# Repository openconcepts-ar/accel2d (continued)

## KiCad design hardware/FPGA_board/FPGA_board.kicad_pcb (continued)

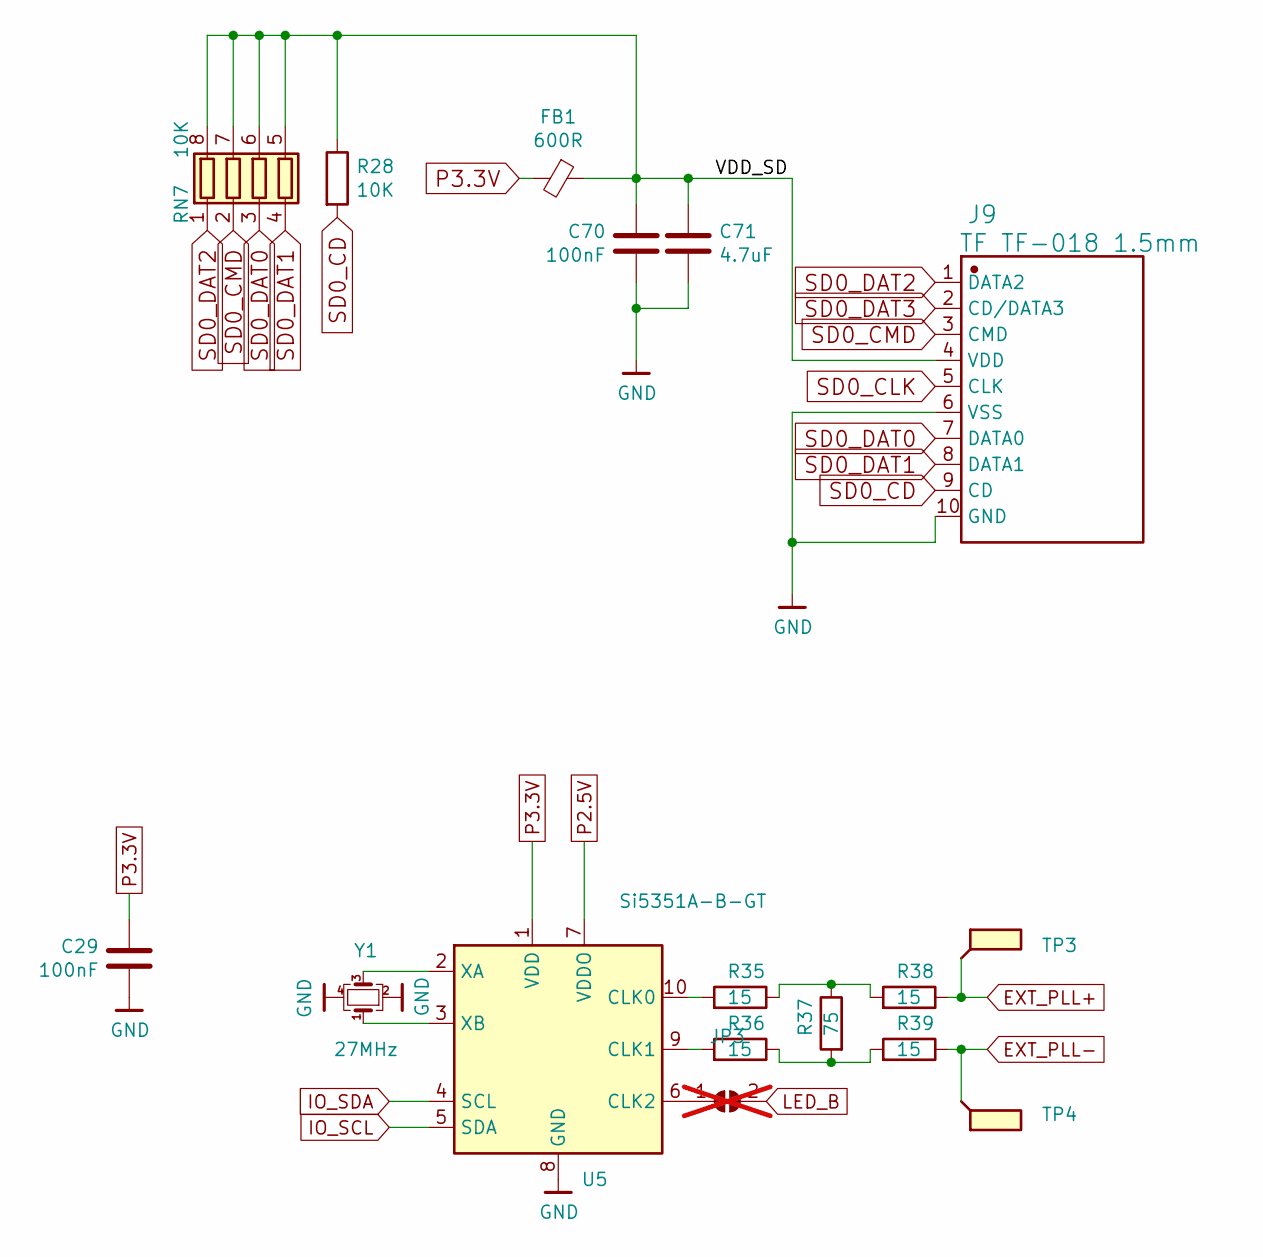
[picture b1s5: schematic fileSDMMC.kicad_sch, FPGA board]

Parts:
C29, C70: 100nF; C_0201_0603Metric; MPN CL03A104KQ3NNNC
C71: 4.7uF; C_0603_1608Metric; MPN CL10A475KP8NNNC
FB1: 600R; L_0402_1005Metric; MPN BLM15AG601SN1D
J9: TF TF-018 1.5mm; TF-SMD_TF-018; MPN TF-018
JP3: SolderJumper_2_Open; SolderJumper-2_P1.3mm_Open_RoundedPad1.0x1.5mm; not fitted
R28: 10K; R_0201_0603Metric
R35, R36, R38, R39: 15; R_0201_0603Metric; MPN RC0201FR-074K7L
R37: 75; R_0201_0603Metric; MPN RC0201FR-074K7L
RN7: 10K; R_Array_Convex_4x0402; MPN 4D02WGJ0103TCE
TP3, TP4: SMD_TP; TestPoint_Pad_D1.0mm
U5: Si5351A-B-GT; MSOP-10_3x3mm_P0.5mm; MPN SI5351A-B-GTR
Y1: 27MHz; Crystal_SMD_2016-4Pin_2.0x1.6mm; MPN XL7EL89COI-111YLC-27M; LCSC Part Number C18214311

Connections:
/sheetSDMMC/VDD_SD: C70.2, C71.1, FB1.1, J9.4 (VDD), R28.1, RN7.5 (R4.2), RN7.6 (R3.2), RN7.7 (R2.2), RN7.8 (R1.2)
EXT_PLL+: R38.1, TP3.1; also elsewhere on the board
EXT_PLL-: R39.1, TP4.1; also elsewhere on the board
GND: C29.1, C70.1, C71.2, J9.6 (VSS), J9.10 (GND), U5.8 (GND), Y1.2, Y1.4; also elsewhere on the board
IO_SCL: U5.5 (SDA); also elsewhere on the board
IO_SDA: U5.4 (SCL); also elsewhere on the board
unnamed: R35.1, R37.1, R38.2
unnamed: R36.1, R37.2, R39.2
unnamed: R35.2, U5.10 (CLK0)
unnamed: R36.2, U5.9 (CLK1)
unnamed: JP3.1 (A), U5.6 (CLK2)
unnamed: U5.2 (XA), Y1.3
unnamed: U5.3 (XB), Y1.1
P2.5V: U5.7 (VDDO); also elsewhere on the board
P3.3V: C29.2, FB1.2, U5.1 (VDD); also elsewhere on the board
SD0_CD: J9.9 (CD), R28.2; also elsewhere on the board
SD0_CLK: J9.5 (CLK); also elsewhere on the board
SD0_CMD: J9.3 (CMD), RN7.2 (R2.1); also elsewhere on the board
SD0_DAT0: J9.7 (DATA0), RN7.3 (R3.1); also elsewhere on the board
SD0_DAT1: J9.8 (DATA1), RN7.4 (R4.1); also elsewhere on the board
SD0_DAT2: J9.1 (DATA2), RN7.1 (R1.1); also elsewhere on the board
SD0_DAT3: J9.2 (CD/DATA3); also elsewhere on the board

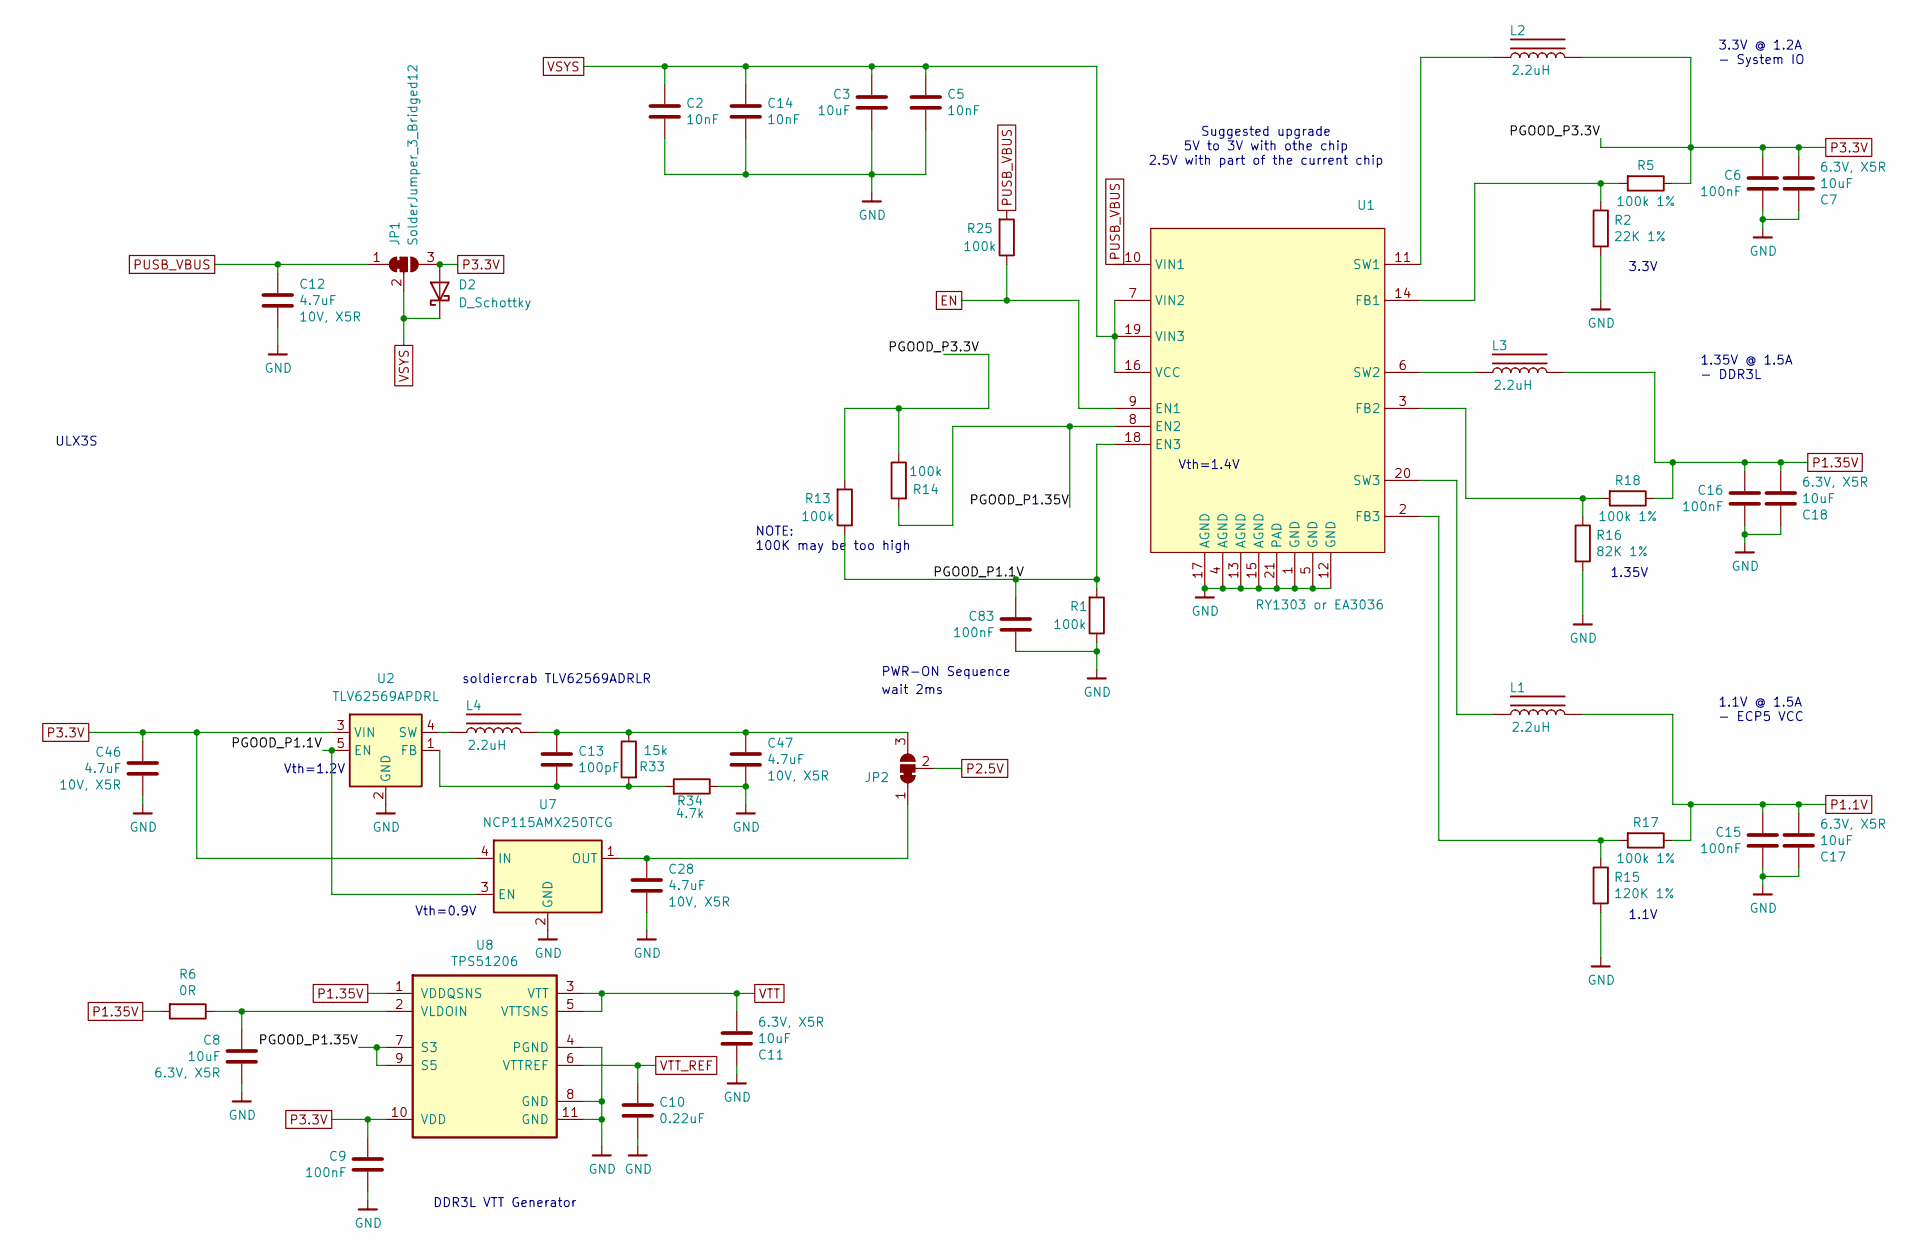
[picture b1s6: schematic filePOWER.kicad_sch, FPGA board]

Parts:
C2, C5, C14: 10nF; C_0201_0603Metric; MPN GRM033R61C103KA12D
C3: 10uF; C_0603_1608Metric; MPN LMK107BBJ106MALT
C6, C9, C15, C16, C83: 100nF; C_0201_0603Metric; MPN CL03A104KQ3NNNC
C7, C8, C11, C17, C18: 10uF; C_0402_1005Metric; MPN GRM155R60J106ME44D
C10: 0.22uF; C_0201_0603Metric; MPN CL03A224MQ3NNNC
C12, C28, C46, C47: 4.7uF; C_0402_1005Metric; MPN GRM155R61A475MEAAD
C13: 100pF; C_0201_0603Metric; MPN GRM033R61C103KA12D
D2: D_Schottky; U-DFN1608-2_L1.6-W0.8-RD; MPN PMEG4020EPK,315
JP1, JP2: SolderJumper_3_Bridged12; SolderJumper-3_P1.3mm_Bridged12_RoundedPad1.0x1.5mm
L1, L2, L3, L4: 2.2uH; Murata_DFE201612P-2R2M=P2; LCSC Part Number C79317
R1, R13, R14, R25: 100k; R_0201_0603Metric; MPN RC0201FR-07100KL
R2: 22K 1%; R_0402_1005Metric
R5, R17, R18: 100k 1%; R_0201_0603Metric; MPN RC0201FR-07100KL
R6: 0R; R_0402_1005Metric; MPN RC0402FR-070RL
R15: 120K 1%; R_0402_1005Metric
R16: 82K 1%; R_0402_1005Metric
R33: 15k; R_0201_0603Metric; MPN RC0201FR-07100KL
R34: 4.7k; R_0201_0603Metric; MPN RC0201FR-07100KL
U1: RY1303 or EA3036; QFN-20-1EP_3x3mm_P0.4mm_EP1.65x1.65mm; MPN EA3036CQBR
U2: TLV62569APDRL; SOT-563; MPN TLV62569APDRLR
U7: NCP115AMX250TCG; OnSemi_XDFN4-1EP_1.0x1.0mm_EP0.52x0.52mm; MPN NCP115AMX250TCG
U8: TPS51206; WSON-10-1EP_2x2mm_P0.4mm; MPN TPS51206DSQR

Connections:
/sheetPower/PGOOD_P1.1V: C83.2, R1.2, R13.1, U1.18 (EN3), U2.5 (EN), U7.3 (EN)
/sheetPower/PGOOD_P1.35V: R14.2, U1.8 (EN2), U8.7 (S3), U8.9 (S5)
EN: R25.1, U1.9 (EN1)
GND: C2.1, C3.1, C5.1, C6.1, C7.2, C8.1, C9.1, C10.1, C11.2, C12.2, C14.1, C15.1, C16.1, C17.2, C18.2, C28.2, C46.2, C47.2, C83.1, R1.1, R2.2, R15.2, R16.2, R34.1, U1.1 (GND), U1.4 (AGND), U1.5 (GND), U1.12 (GND), U1.13 (AGND), U1.15 (AGND), U1.17 (AGND), U1.21 (PAD), U2.2 (GND), U7.2 (GND), U7.5 (GND), U8.4 (PGND), U8.8 (GND), U8.11 (GND); also elsewhere on the board
unnamed: C28.1, JP2.1 (A), U7.1 (OUT)
unnamed: C13.2, C47.1, JP2.3 (B), L4.1, R33.1
unnamed: R2.1, R5.2, U1.14 (FB1)
unnamed: R16.1, R18.2, U1.3 (FB2)
unnamed: R15.1, R17.2, U1.2 (FB3)
unnamed: L2.2, U1.11 (SW1)
unnamed: L3.2, U1.6 (SW2)
unnamed: L1.2, U1.20 (SW3)
unnamed: C13.1, R33.2, R34.2, U2.1 (FB)
unnamed: L4.2, U2.4 (SW)
unnamed: C8.2, R6.1, U8.2 (VLDOIN)
P1.1V: C15.2, C17.1, L1.1, R17.1; also elsewhere on the board
P1.35V: C16.2, C18.1, L3.1, R6.2, R18.1, U8.1 (VDDQSNS); also elsewhere on the board
P2.5V: JP2.2 (C); also elsewhere on the board
P3.3V: C6.2, C7.1, C9.2, C46.1, D2.2 (A), JP1.3 (B), L2.1, R5.1, R13.2, R14.1, U2.3 (VIN), U7.4 (IN), U8.10 (VDD); also elsewhere on the board
PUSB_VBUS: C12.1, JP1.1 (A), R25.2, U1.10 (VIN1); also elsewhere on the board
VSYS: C2.2, C3.2, C5.2, C14.2, D2.1 (K), JP1.2 (C), U1.7 (VIN2), U1.16 (VCC), U1.19 (VIN3)
VTT: C11.1, U8.3 (VTT), U8.5 (VTTSNS); also elsewhere on the board
VTT_REF: C10.2, U8.6 (VTTREF); also elsewhere on the board

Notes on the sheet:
1.1V @ 1.5A - ECP5 VCC
PWR-ON Sequence
Vth=0.9V
NOTE: 100K may be too high
1.35V @ 1.5A - DDR3L
soldiercrab TLV62569ADRLR
DDR3L VTT Generator
Suggested upgrade 5V to 3V with othe chip 2.5V with part of the current chip
1.1V
3.3V @ 1.2A - System IO
3.3V
wait 2ms
Vth=1.4V
ULX3S
1.35V
Vth=1.2V

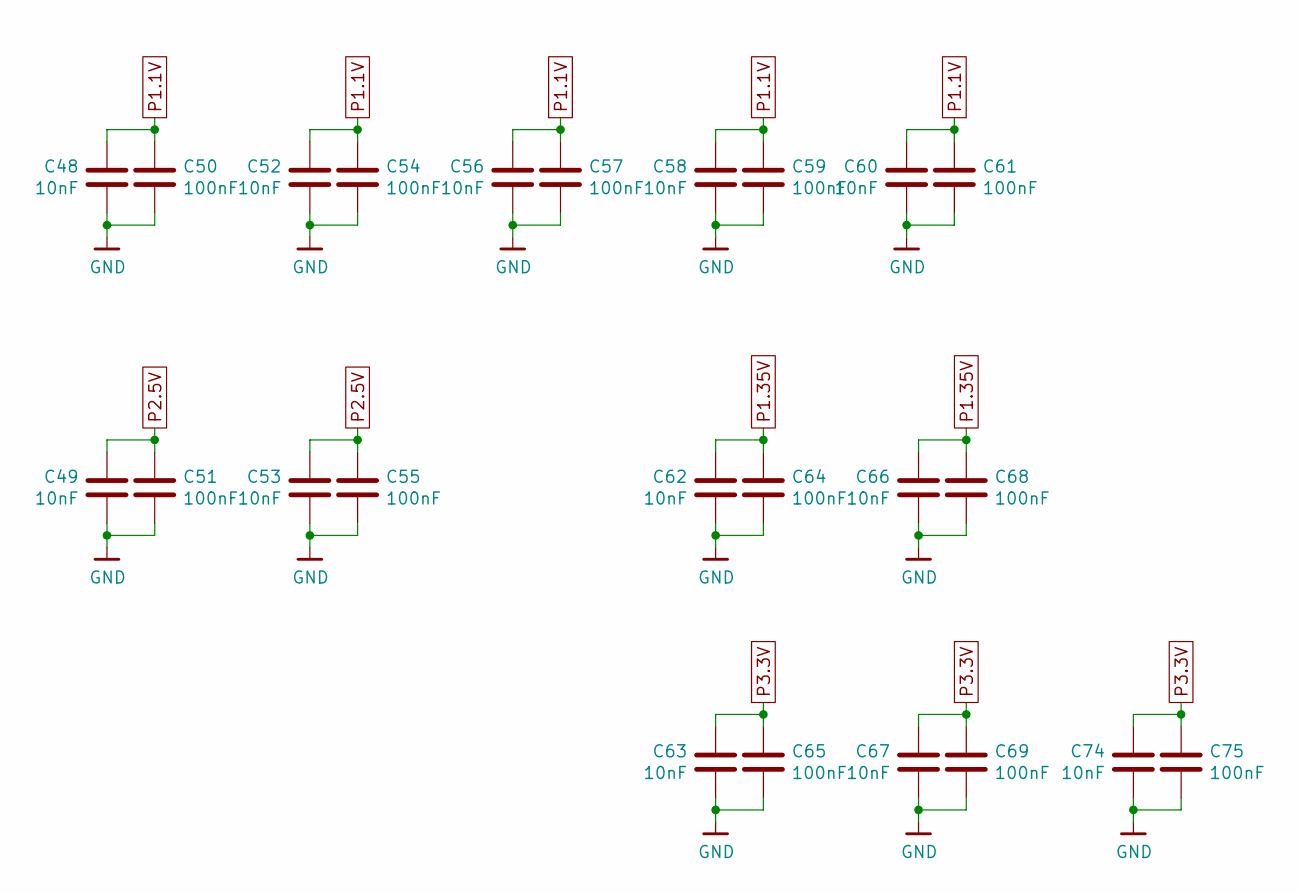
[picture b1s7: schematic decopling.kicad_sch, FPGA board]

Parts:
C48, C49, C52, C53, C56, C58, C60, C62, C63, C66, C67, C74: 10nF; C_0201_0603Metric; MPN GRM033R61C103KA12D
C50, C51, C54, C55, C57, C59, C61, C64, C65, C68, C69, C75: 100nF; C_0201_0603Metric; MPN CL03A104KQ3NNNC

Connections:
GND: C48.2, C49.2, C50.2, C51.2, C52.2, C53.2, C54.2, C55.2, C56.2, C57.2, C58.2, C59.2, C60.2, C61.2, C62.2, C63.2, C64.2, C65.2, C66.2, C67.2, C68.2, C69.2, C74.2, C75.2; also elsewhere on the board
P1.1V: C48.1, C50.1, C52.1, C54.1, C56.1, C57.1, C58.1, C59.1, C60.1, C61.1; also elsewhere on the board
P1.35V: C62.1, C64.1, C66.1, C68.1; also elsewhere on the board
P2.5V: C49.1, C51.1, C53.1, C55.1; also elsewhere on the board
P3.3V: C63.1, C65.1, C67.1, C69.1, C74.1, C75.1; also elsewhere on the board

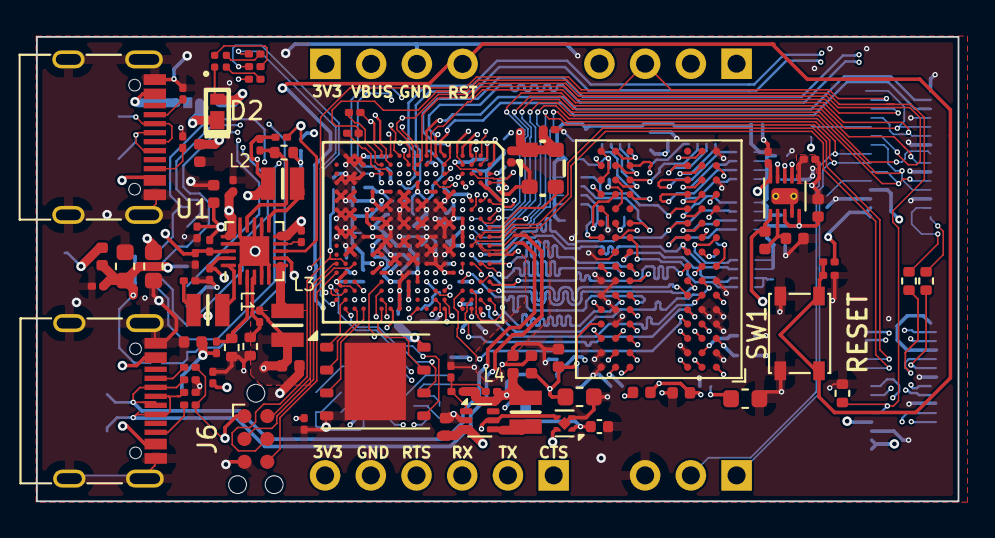
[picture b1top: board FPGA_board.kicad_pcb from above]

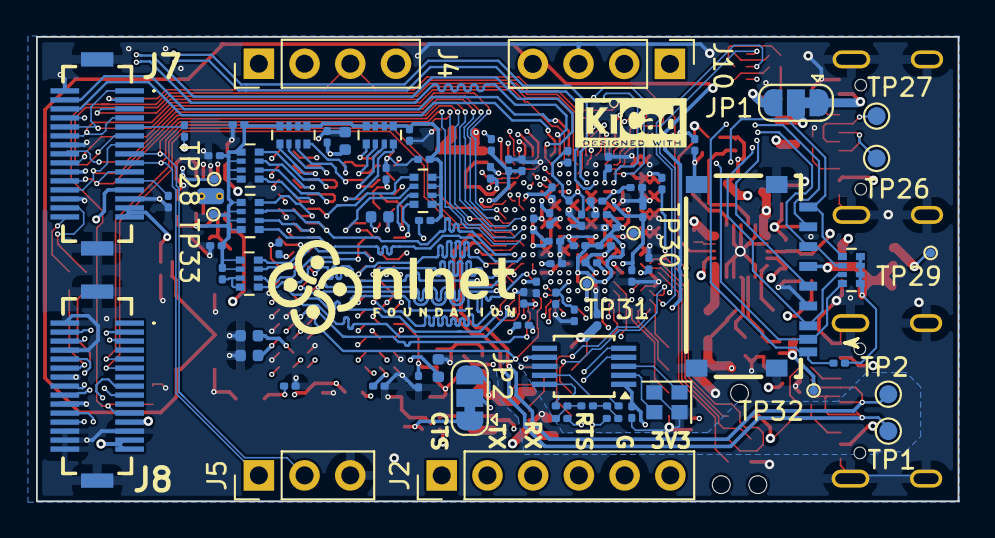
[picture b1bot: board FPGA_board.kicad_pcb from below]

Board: 6 copper layers, 51.2 x 25.8 mm, 163 parts (86 on the bottom side), 154 nets.

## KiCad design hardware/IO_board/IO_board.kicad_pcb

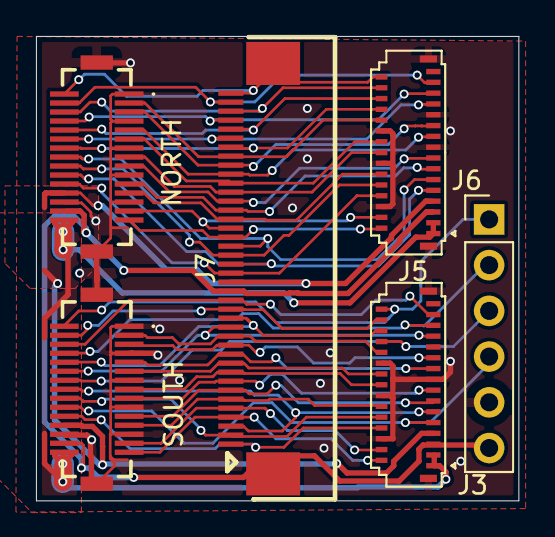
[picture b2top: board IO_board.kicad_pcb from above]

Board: 2 copper layers, 26.8 x 25.8 mm, 6 parts (0 on the bottom side), 46 nets.

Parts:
J1, J4: DF12NB(3.0)-30DS-0.5V(51); DF12NB3030DP05V51
J3, J5: Conn_01x31; Hirose_FH26-31S-0.3SHW_2Rows-31Pins-1MP_P0.60mm_Horizontal
J6: Conn_01x06; PinHeader_1x06_P2.54mm_Vertical
J7: Combined I/O; FPC-SMD_40P-P0.50_L4.4-W25.6

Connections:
/3V3: J1.30 (29), J3.1, J3.3, J4.30 (29), J5.1, J5.3
/5V0: J1.24 (23), J3.7, J4.24 (23), J5.7, J7.19
/B0: J1.8 (7), J5.27, J7.37
/B1: J1.2 (1), J5.30, J7.40
/B6: J1.27 (28), J5.4, J7.25
/B7: J1.29 (30), J5.2, J7.24
/BL_EN: J3.26, J4.10 (9), J7.15
/BL_PWM: J3.25, J4.12 (11), J7.14
/CK+: J3.22, J4.3 (4), J7.13
/CK-: J3.21, J4.5 (6), J7.12
/DE: J1.6 (5), J5.28, J7.38
/G0: J1.20 (19), J5.9, J7.21
/G1: J1.14 (13), J5.24, J7.34
/G4: J3.29, J4.6 (5), J7.17
/G5: J3.28, J4.4 (3), J7.16
/HPD2: J3.8, J4.22 (21), J7.1
/HPD/ID: J1.22 (21), J5.8, J7.20
/HSYNC: J1.10 (9), J5.26, J7.36
/LVDS_E0+: J3.13, J4.21 (22), J7.7
/LVDS_E0-: J3.12, J4.23 (24), J7.6
/LVDS_E1+: J3.16, J4.15 (16), J7.9
/LVDS_E1-: J3.15, J4.17 (18), J7.8
/LVDS_E2+: J3.19, J4.9 (10), J7.11
/LVDS_E2-: J3.18, J4.11 (12), J7.10
/LVDS_O0+: J1.21 (22), J5.13, J7.27
/LVDS_O0-: J1.23 (24), J5.12, J7.26
/LVDS_O1+: J1.15 (16), J5.16, J7.29
/LVDS_O1-: J1.17 (18), J5.15, J7.28
/LVDS_O2+: J1.9 (10), J5.19, J7.31
/LVDS_O2-: J1.11 (12), J5.18, J7.30
/LVDS_OC+: J1.3 (4), J5.22, J7.33
/LVDS_OC-: J1.5 (6), J5.21, J7.32
/PCLK: J1.4 (3), J5.29, J7.39
/R0: J3.4, J4.27 (28), J7.5
/R1: J3.2, J4.29 (30), J7.4
/SCL: J1.18 (17), J5.10, J7.22
/SCL2: J3.10, J4.18 (17), J7.2
/SDA: J1.16 (15), J5.11, J7.23
/SDA2: J3.11, J4.16 (15), J7.3
/TP_X1: J3.9, J4.20 (19), J6.4
/TP_X2: J3.24, J4.14 (13), J6.3
/TP_Y1: J3.30, J4.2 (1), J6.1
/TP_Y2: J3.27, J4.8 (7), J6.2
/VIO: J1.28 (27), J3.5, J4.28 (27), J5.5, J6.6, J7.18
/VSYNC: J1.12 (11), J5.25, J7.35
GND: J1.1 (2), J1.7 (8), J1.13 (14), J1.19 (20), J1.25 (26), J1.26 (25), J1.MP1, J1.MP2, J3.6, J3.14, J3.17, J3.20, J3.23, J3.MP (MountPin), J4.1 (2), J4.7 (8), J4.13 (14), J4.19 (20), J4.25 (26), J4.26 (25), J4.MP1, J4.MP2, J5.6, J5.14, J5.17, J5.20, J5.23, J5.MP (MountPin), J6.5

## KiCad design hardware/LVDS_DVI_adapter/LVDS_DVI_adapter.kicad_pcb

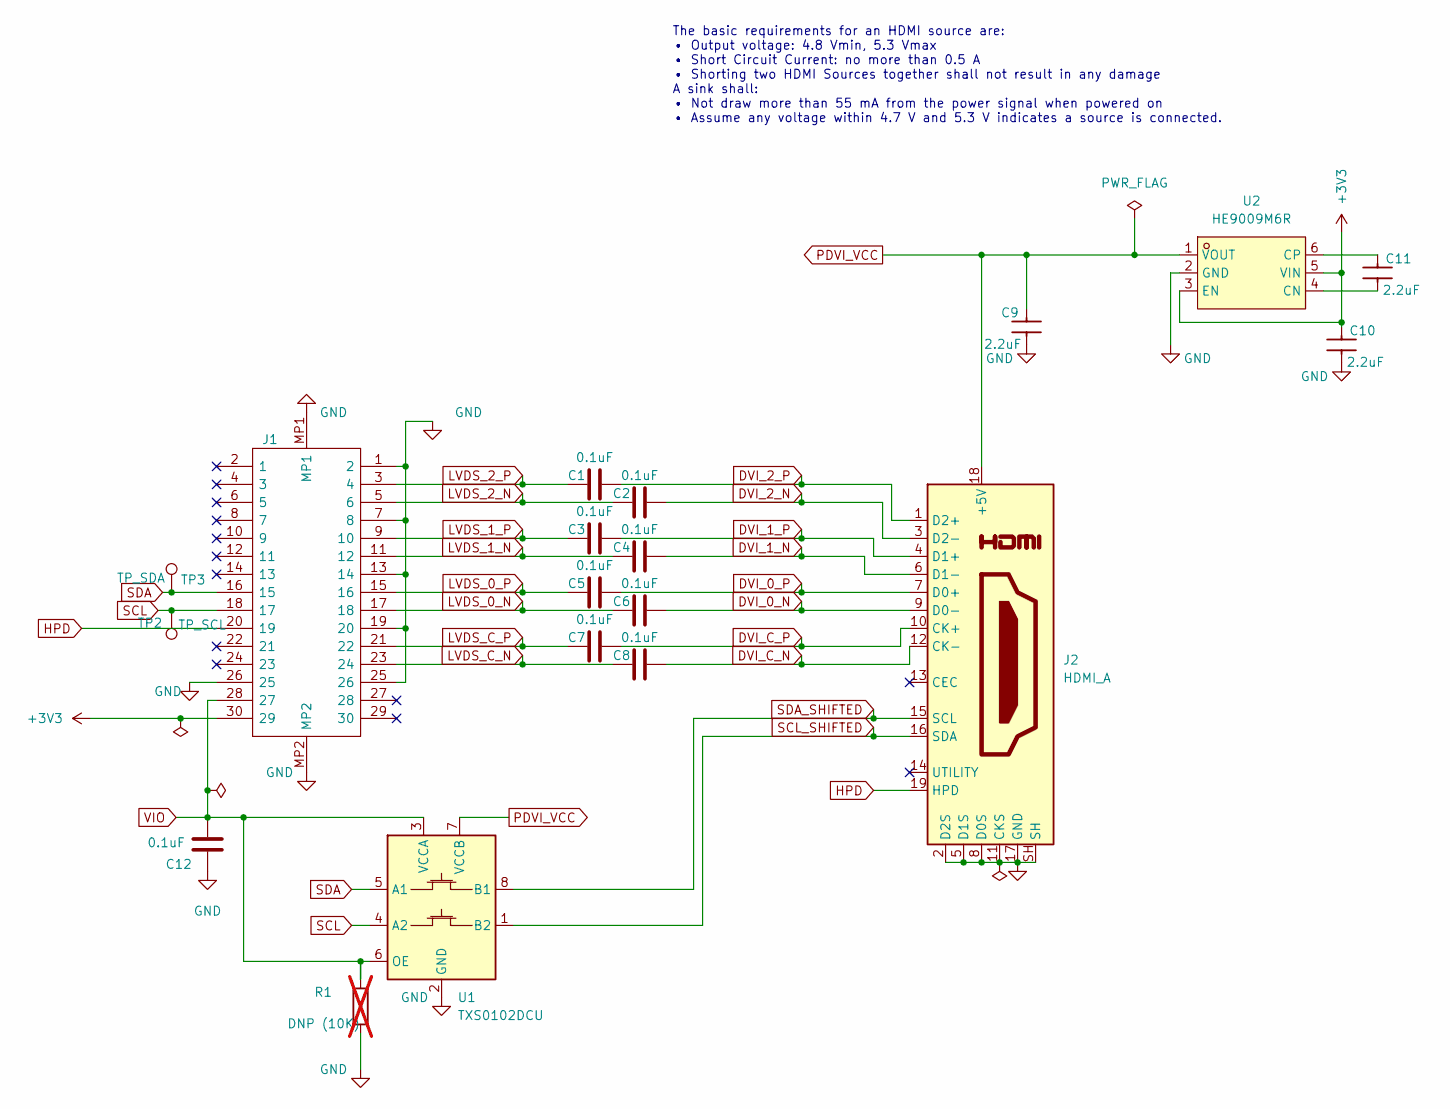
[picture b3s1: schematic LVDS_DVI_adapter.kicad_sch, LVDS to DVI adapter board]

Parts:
C1, C2, C3, C4, C5, C6, C8, C12: 0.1uF; C_0402_1005Metric; LCSC Part number C60474
C7: 0.1uF; C_0402_1005Metric; LCSC Part Number C60474
C9, C10, C11: 2.2uF; C_0402_1005Metric; LCSC Part Number C170151
J1: DF12NB(3.0)-30DS-0.5V(51); DF12NB3030DP05V51; Manufacturer_Part_Number DF12NB(3.0)-30DP-0.5V(51); LCSC Part Number C2904115
J2: HDMI_A; HDMI_A_Amphenol_10029449-x01xLF_Horizontal; LCSC Part number C427307
R1: DNP (10K); R_0402_1005Metric; LCSC Part Number C25531; not fitted
TP2: TP_SCL; TestPoint_THTPad_1.0x1.0mm_Drill0.5mm
TP3: TP_SDA; TestPoint_THTPad_1.0x1.0mm_Drill0.5mm
U1: TXS0102DCU; VSSOP-8_2.3x2mm_P0.5mm; LCSC Part Number C53434
U2: HE9009M6R; SOT-23-6; MPN HE9009M6R

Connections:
+3V3: C10.1, J1.30 (29), U2.3 (EN), U2.5 (VIN)
DVI_0_N: C6.2, J2.9 (D0-)
DVI_0_P: C5.2, J2.7 (D0+)
DVI_1_N: C4.2, J2.6 (D1-)
DVI_1_P: C3.2, J2.4 (D1+)
DVI_2_N: C2.2, J2.3 (D2-)
DVI_2_P: C1.2, J2.1 (D2+)
DVI_C_N: C8.2, J2.12 (CK-)
DVI_C_P: C7.2, J2.10 (CK+)
GND: C9.2, C10.2, C12.1, J1.1 (2), J1.7 (8), J1.13 (14), J1.19 (20), J1.25 (26), J1.26 (25), J1.MP1, J1.MP2, J2.2 (D2S), J2.5 (D1S), J2.8 (D0S), J2.11 (CKS), J2.17 (GND), J2.SH, R1.2, U1.2 (GND), U2.2 (GND)
HPD: J1.20 (19), J2.19 (HPD)
LVDS_0_N: C6.1, J1.17 (18)
LVDS_0_P: C5.1, J1.15 (16)
LVDS_1_N: C4.1, J1.11 (12)
LVDS_1_P: C3.1, J1.9 (10)
LVDS_2_N: C2.1, J1.5 (6)
LVDS_2_P: C1.1, J1.3 (4)
LVDS_C_N: C8.1, J1.23 (24)
LVDS_C_P: C7.1, J1.21 (22)
unnamed: C11.2, U2.4 (CN)
unnamed: C11.1, U2.6 (CP)
PDVI_VCC: C9.1, J2.18 (+5V), U1.7 (VCCB), U2.1 (VOUT)
SCL: J1.18 (17), TP2.1, U1.4 (A2)
SCL_SHIFTED: J2.16 (SDA), U1.1 (B2)
SDA: J1.16 (15), TP3.1, U1.5 (A1)
SDA_SHIFTED: J2.15 (SCL), U1.8 (B1)
VIO: C12.2, J1.28 (27), R1.1, U1.3 (VCCA), U1.6 (OE)

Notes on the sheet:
The basic requirements for an HDMI source are: • Output voltage: 4.8 Vmin, 5.3 Vmax • Short Circuit Current: no more than 0.5 A • Shorting two HDMI Sources together shall not result in any damage A sink shall: • Not draw more than 55 mA from the power signal when powered on • Assume any voltage wit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

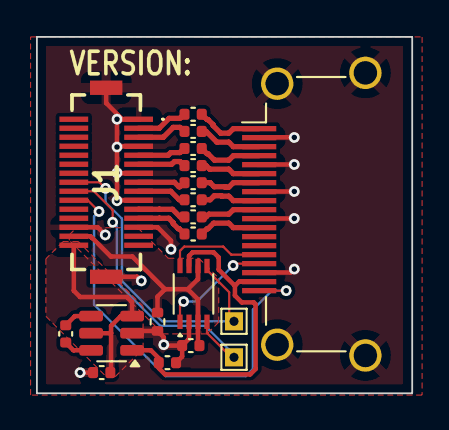
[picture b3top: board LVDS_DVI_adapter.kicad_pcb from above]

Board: 2 copper layers, 20.9 x 19.8 mm, 19 parts (0 on the bottom side), 27 nets.

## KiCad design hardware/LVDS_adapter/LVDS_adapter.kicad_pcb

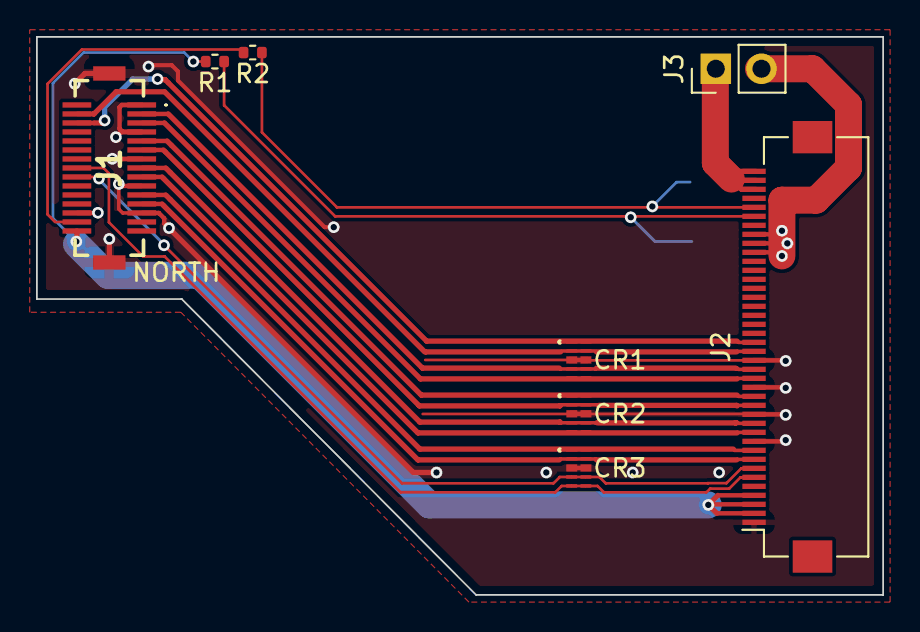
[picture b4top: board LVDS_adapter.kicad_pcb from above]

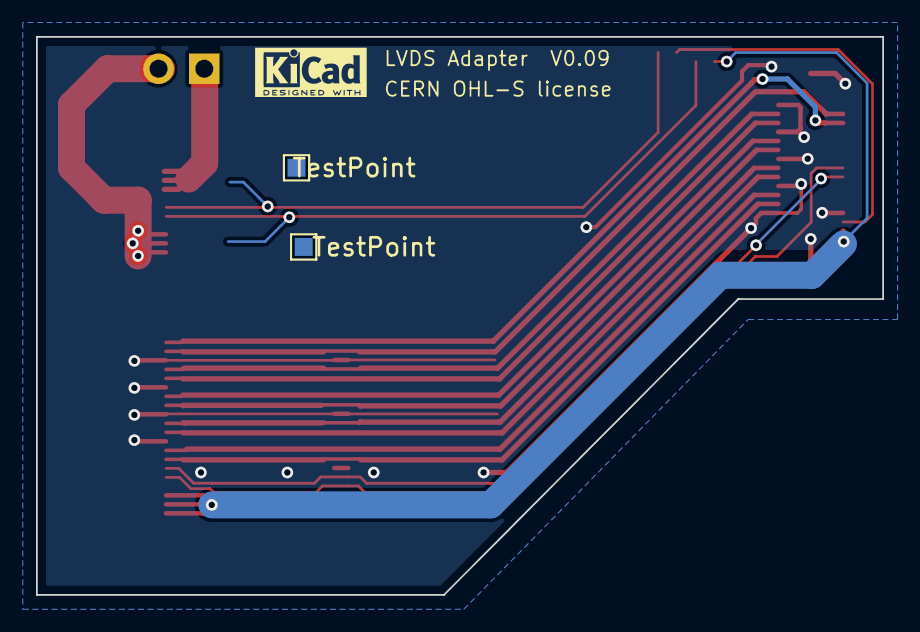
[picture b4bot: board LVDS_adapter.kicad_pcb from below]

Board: 2 copper layers, 47.0 x 31.0 mm, 10 parts (2 on the bottom side), 19 nets.

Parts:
CR1, CR2, CR3: ESD7004MUTAG; UDFN10_517BB_ONS-L
J1: DF12NB(3.0)-30DS-0.5V(51); DF12NB3030DP05V51
J2: LVDS; Hirose_FH12-40S-0.5SH_1x40-1MP_P0.50mm_Horizontal
J3: BAKLIGHT_POWER; PinHeader_1x02_P2.54mm_Vertical
R1, R2: 10K; R_0402_1005Metric
TP1, TP2: TestPoint; TestPoint_Pad_1.0x1.0mm

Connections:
GND: CR1.3, CR1.8, CR2.3, CR2.8, CR3.3, CR3.8, J1.1 (2), J1.7 (8), J1.13 (14), J1.19 (20), J1.25 (26), J1.26 (25), J1.MP1, J1.MP2, J2.1, J2.10, J2.13, J2.16, J2.19
LED_VCC: J2.38, J2.39, J2.40, J3.1
LVDS_O0_N: CR3.2, CR3.9, J1.23 (24), J2.8
LVDS_O0_P: CR3.1, CR3.10, J1.21 (22), J2.9
LVDS_O1_N: CR2.5, CR2.6, J1.17 (18), J2.11
LVDS_O1_P: CR2.4, CR2.7, J1.15 (16), J2.12
LVDS_O2_N: CR2.2, CR2.9, J1.11 (12), J2.14
LVDS_O2_P: CR2.1, CR2.10, J1.9 (10), J2.15
LVDS_O3_N: CR1.2, CR1.9, J1.4 (3), J2.20
LVDS_O3_P: CR1.1, CR1.10, J1.6 (5), J2.21
LVDS_OC_N: CR1.5, CR1.6, J1.5 (6), J2.17
LVDS_OC_P: CR1.4, CR1.7, J1.3 (4), J2.18
unnamed: J1.28 (27), R2.2
unnamed: J2.31, J2.32, J2.33, J3.2
unnamed: J2.35, R1.1, TP2.1
unnamed: J2.36, R2.1, TP1.1
SCL: CR3.4, CR3.7, J1.18 (17), J2.7
SDA: CR3.5, CR3.6, J1.16 (15), J2.6
VCC: J1.30 (29), J2.2, J2.3, J2.4, R1.2

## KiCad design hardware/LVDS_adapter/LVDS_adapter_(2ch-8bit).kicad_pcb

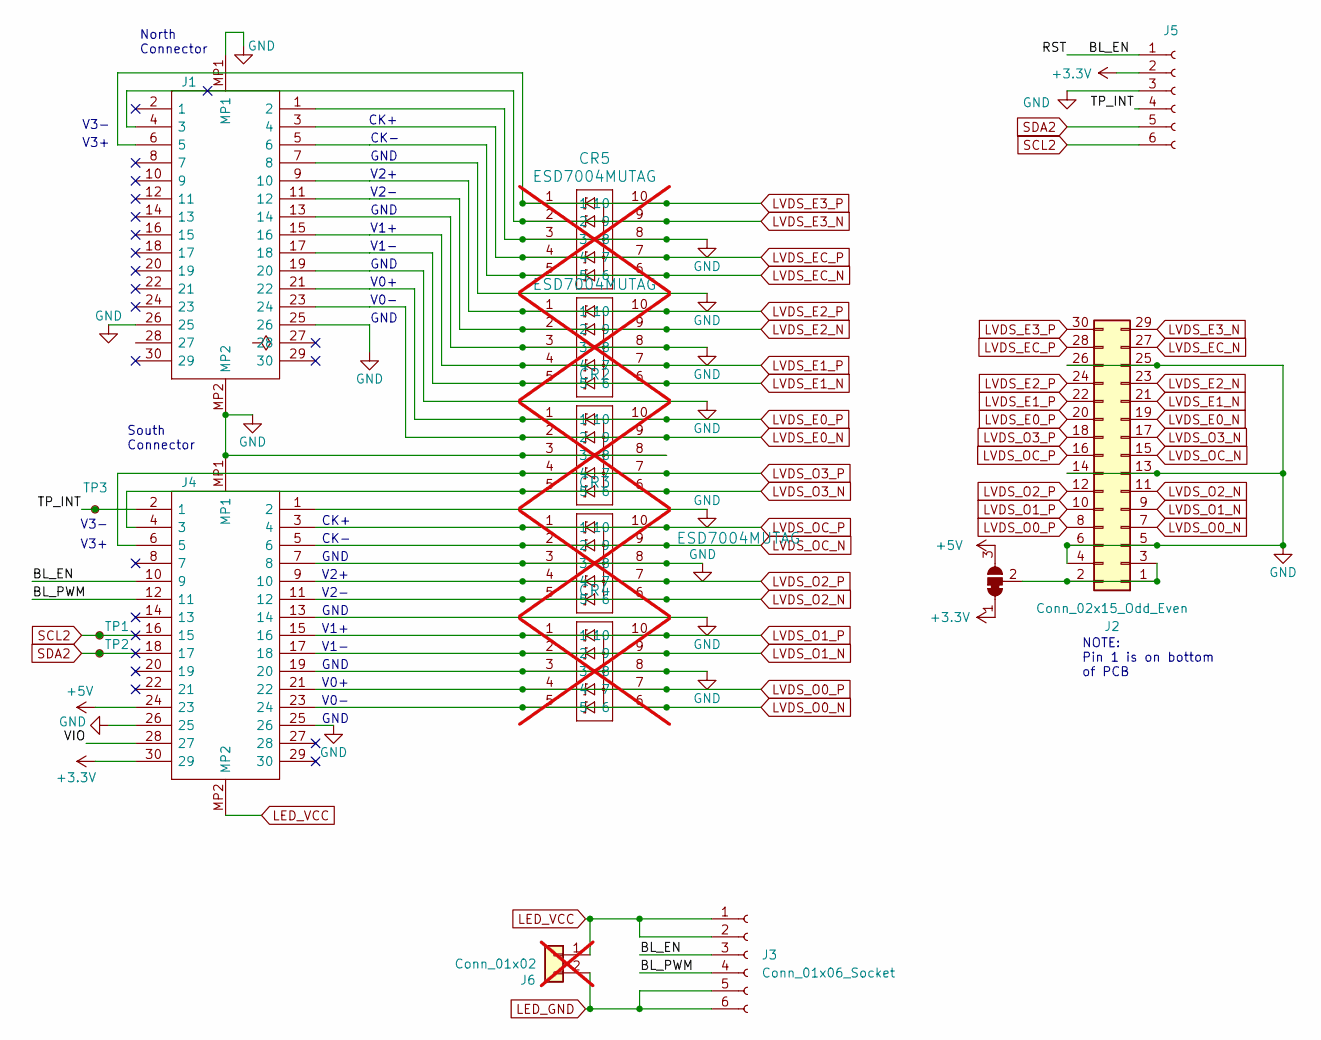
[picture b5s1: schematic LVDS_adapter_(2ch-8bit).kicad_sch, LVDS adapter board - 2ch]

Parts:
CR1, CR2, CR3, CR4, CR5: ESD7004MUTAG; Diodes_UDFN-10_1.0x2.5mm_P0.5mm; LCSC Part Number C2931115; not fitted
J1, J4: DF12NB(3.0)-30DS-0.5V(51); DF12NB3030DP05V51; Manufacturer_Part_Number DF12NB(3.0)-30DP-0.5V(51); LCSC Part Number C2904115
J2: Conn_02x15_Odd_Even; PinHeader_2x15_P2.00mm_Vertical
J3: Conn_01x06_Socket; JST_PH_S6B-PH-K_1x06_P2.00mm_Horizontal; MPN S6B-PH-K-S(LF)(SN)
J5: Conn_01x06_Socket; FPC-SMD_FH52K-6S-0.5SH; MPN FH52K-6S-0.5SH
J6: Conn_01x02; PinHeader_1x02_P2.54mm_Vertical; not fitted
JP1: SolderJumper_3_Bridged12; SolderJumper-3_P1.3mm_Bridged12_RoundedPad1.0x1.5mm
TP1, TP2, TP3: TestPoint_Small; TestPoint_Pad_D1.0mm

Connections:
+3.3V: J4.30 (29), J5.2, JP1.1 (A)
+5V: J4.24 (23), JP1.3 (B)
/BL_EN: J3.3, J4.10 (9), J5.1
/BL_PWM: J3.4, J4.12 (11)
/TP_INT: J4.2 (1), J5.4, TP3.1
/VIO: J4.28 (27)
GND: CR1.3, CR1.8, CR2.3, CR2.8, CR3.3, CR3.8, CR4.3, CR4.8, CR5.3, CR5.8, J1.1 (2), J1.7 (8), J1.13 (14), J1.19 (20), J1.25 (26), J1.26 (25), J1.MP1, J1.MP2, J2.4, J2.5, J2.6, J2.13, J2.14, J2.25, J2.26, J4.1 (2), J4.7 (8), J4.13 (14), J4.19 (20), J4.25 (26), J4.26 (25), J4.MP1, J5.3
LED_GND: J3.5, J3.6, J6.2
LED_VCC: J3.1, J3.2, J4.MP2, J6.1
LVDS_E0_N: CR2.2, CR2.9, J1.23 (24), J2.19
LVDS_E0_P: CR2.1, CR2.10, J1.21 (22), J2.20
LVDS_E1_N: CR1.5, CR1.6, J1.17 (18), J2.21
LVDS_E1_P: CR1.4, CR1.7, J1.15 (16), J2.22
LVDS_E2_N: CR1.2, CR1.9, J1.11 (12), J2.23
LVDS_E2_P: CR1.1, CR1.10, J1.9 (10), J2.24
LVDS_E3_N: CR5.2, CR5.9, J1.4 (3), J2.29
LVDS_E3_P: CR5.1, CR5.10, J1.6 (5), J2.30
LVDS_EC_N: CR5.5, CR5.6, J1.5 (6), J2.27
LVDS_EC_P: CR5.4, CR5.7, J1.3 (4), J2.28
LVDS_O0_N: CR4.5, CR4.6, J2.7, J4.23 (24)
LVDS_O0_P: CR4.4, CR4.7, J2.8, J4.21 (22)
LVDS_O1_N: CR4.2, CR4.9, J2.9, J4.17 (18)
LVDS_O1_P: CR4.1, CR4.10, J2.10, J4.15 (16)
LVDS_O2_N: CR3.5, CR3.6, J2.11, J4.11 (12)
LVDS_O2_P: CR3.4, CR3.7, J2.12, J4.9 (10)
LVDS_O3_N: CR2.5, CR2.6, J2.17, J4.4 (3)
LVDS_O3_P: CR2.4, CR2.7, J2.18, J4.6 (5)
LVDS_OC_N: CR3.2, CR3.9, J2.15, J4.5 (6)
LVDS_OC_P: CR3.1, CR3.10, J2.16, J4.3 (4)
unnamed: J2.1, J2.2, J2.3, JP1.2 (C)
SCL2: J4.16 (15), J5.6, TP1.1
SDA2: J4.18 (17), J5.5, TP2.1

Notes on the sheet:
CK+
GND
V3-
V1-
North Connector
V0+
V2-
V0-
CK-
V1+
V3+
NOTE: Pin 1 is on bottom of PCB
South Connector
V2+

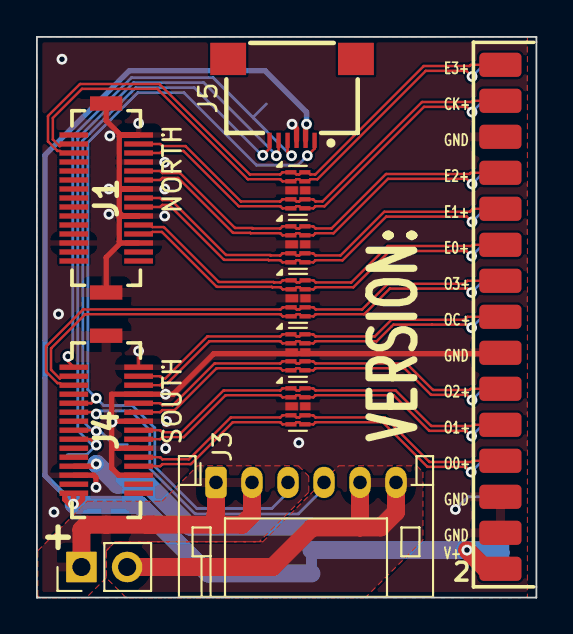
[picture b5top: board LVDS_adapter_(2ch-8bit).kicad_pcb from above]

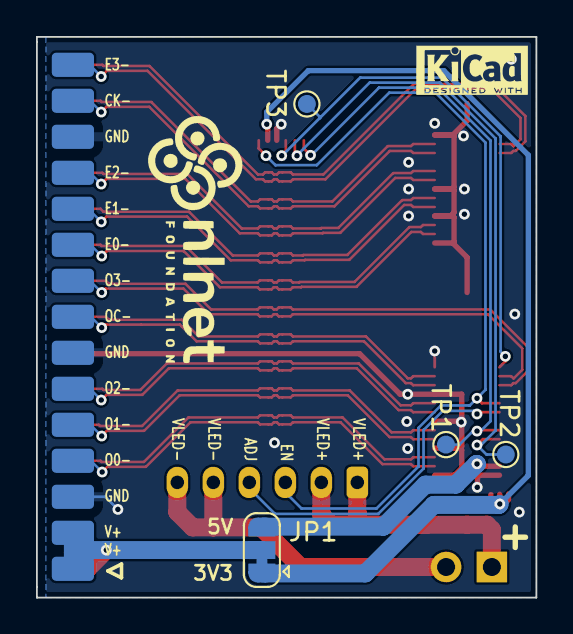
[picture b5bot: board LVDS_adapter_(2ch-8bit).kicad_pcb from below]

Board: 2 copper layers, 27.8 x 31.1 mm, 15 parts (4 on the bottom side), 31 nets.

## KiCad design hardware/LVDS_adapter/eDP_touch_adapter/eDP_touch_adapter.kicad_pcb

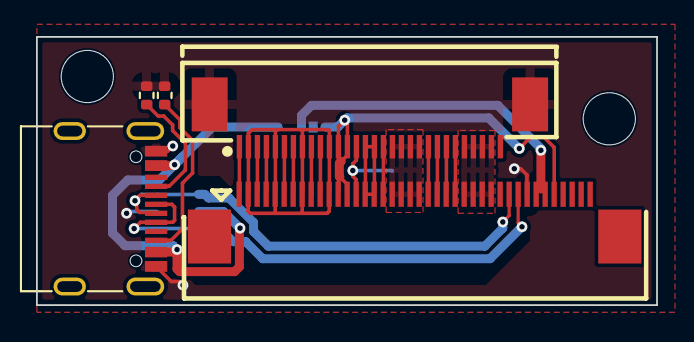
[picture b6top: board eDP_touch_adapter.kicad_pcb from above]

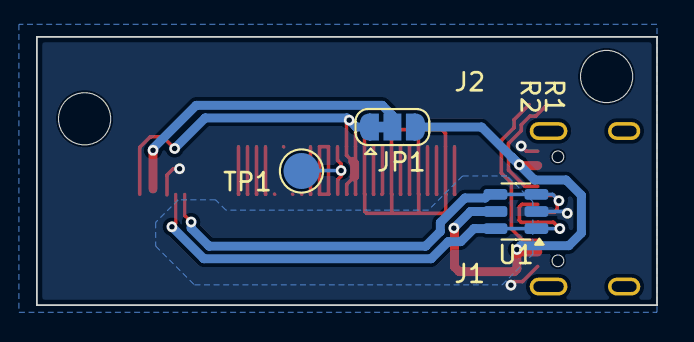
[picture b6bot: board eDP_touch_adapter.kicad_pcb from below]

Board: 2 copper layers, 34.4 x 14.9 mm, 10 parts (3 on the bottom side), 22 nets.

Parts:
H1, H2: MountingHole; MountingHole_2.2mm_M2_ISO7380
J1: Conn_01x40; FPC-SMD_40P-P0.50_L4.4-W25.6
J2: Conn_01x30; FPC-SMD_30P-P0.50_L4.4-W20.6
JP1: SolderJumper_3_Bridged12; SolderJumper-3_P1.3mm_Bridged12_RoundedPad1.0x1.5mm
R1, R2: 5.1k; R_0402_1005Metric
TP1: TestPoint_Small; TestPoint_Pad_D2.0mm
U1: USBLC6-2SC6; SOT-23-6
USB1: USB_C_Receptacle_USB2.0; USB_C_Receptacle_G-Switch_GT-USB-7010ASV

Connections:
+3V3: J1.12, J1.13, J1.36, J2.12, J2.13, JP1.1 (A)
+5V: JP1.3 (B), U1.5 (VBUS), USB1.A4 (VBUS), USB1.A9 (VBUS), USB1.B4 (VBUS), USB1.B9 (VBUS)
/AUX_N: J1.10, J2.10
/AUX_P: J1.9, J2.9
/BL_EN: J1.22, J2.22
/BL_GND: J1.18, J1.19, J1.20, J1.21, J2.18, J2.19, J2.20, J2.21
/BL_PWM: J1.23, J2.23
/BL_PWR: J1.26, J1.27, J1.28, J1.29, J2.26, J2.27, J2.28, J2.29
/EDP0_N: J1.6, J2.6
/EDP1_N: J1.3, J2.3
/EDP1_P: J1.4, J2.4
/EDPO_P: J1.7, J2.7
/HGND: J1.2, J1.5, J1.8, J1.11, J2.2, J2.5, J2.8, J2.11
/HPD: J1.17, J2.17
/LCD_GND: J1.15, J1.16, J2.15, J2.16
/TEST: J1.14, J2.14, TP1.1
/VTSP: J1.34, J1.35, JP1.2 (C)
GND: J1.33, J2.MP (MountPin), R1.2, R2.2, U1.2 (GND), USB1.A1 (GND), USB1.A12 (GND), USB1.B1 (GND), USB1.B12 (GND)
unnamed: R1.1, USB1.A5 (CC1)
unnamed: R2.1, USB1.B5 (CC2)
TP_D+: J1.32, U1.1 (I/O1), U1.6 (I/O1), USB1.A6 (D+), USB1.B6 (D+)
TP_D-: J1.31, U1.3 (I/O2), U1.4 (I/O2), USB1.A7 (D-), USB1.B7 (D-)
